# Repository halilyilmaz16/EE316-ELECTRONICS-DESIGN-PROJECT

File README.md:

# Capacitive Water Level Controller

An analog closed-loop water level control system designed and implemented
for the EE 316 Electronic Design Project at İzmir Institute of Technology.

The system detects liquid-level variations using a custom cylindrical
capacitive sensor. The sensor output is processed through phase detection,
filtering, amplification, error generation, and PWM stages. The resulting
PWM signal controls a submersible DC water pump through an L298N motor driver.

## Key Features

- Custom cylindrical capacitive water-level sensor
- TLC555-based oscillator
- XOR-based phase detection
- RC filtering and LM358 signal amplification
- Adjustable reference water level
- PWM-based pump speed control
- Motor overcurrent protection
- LTspice simulation and real-world circuit testing

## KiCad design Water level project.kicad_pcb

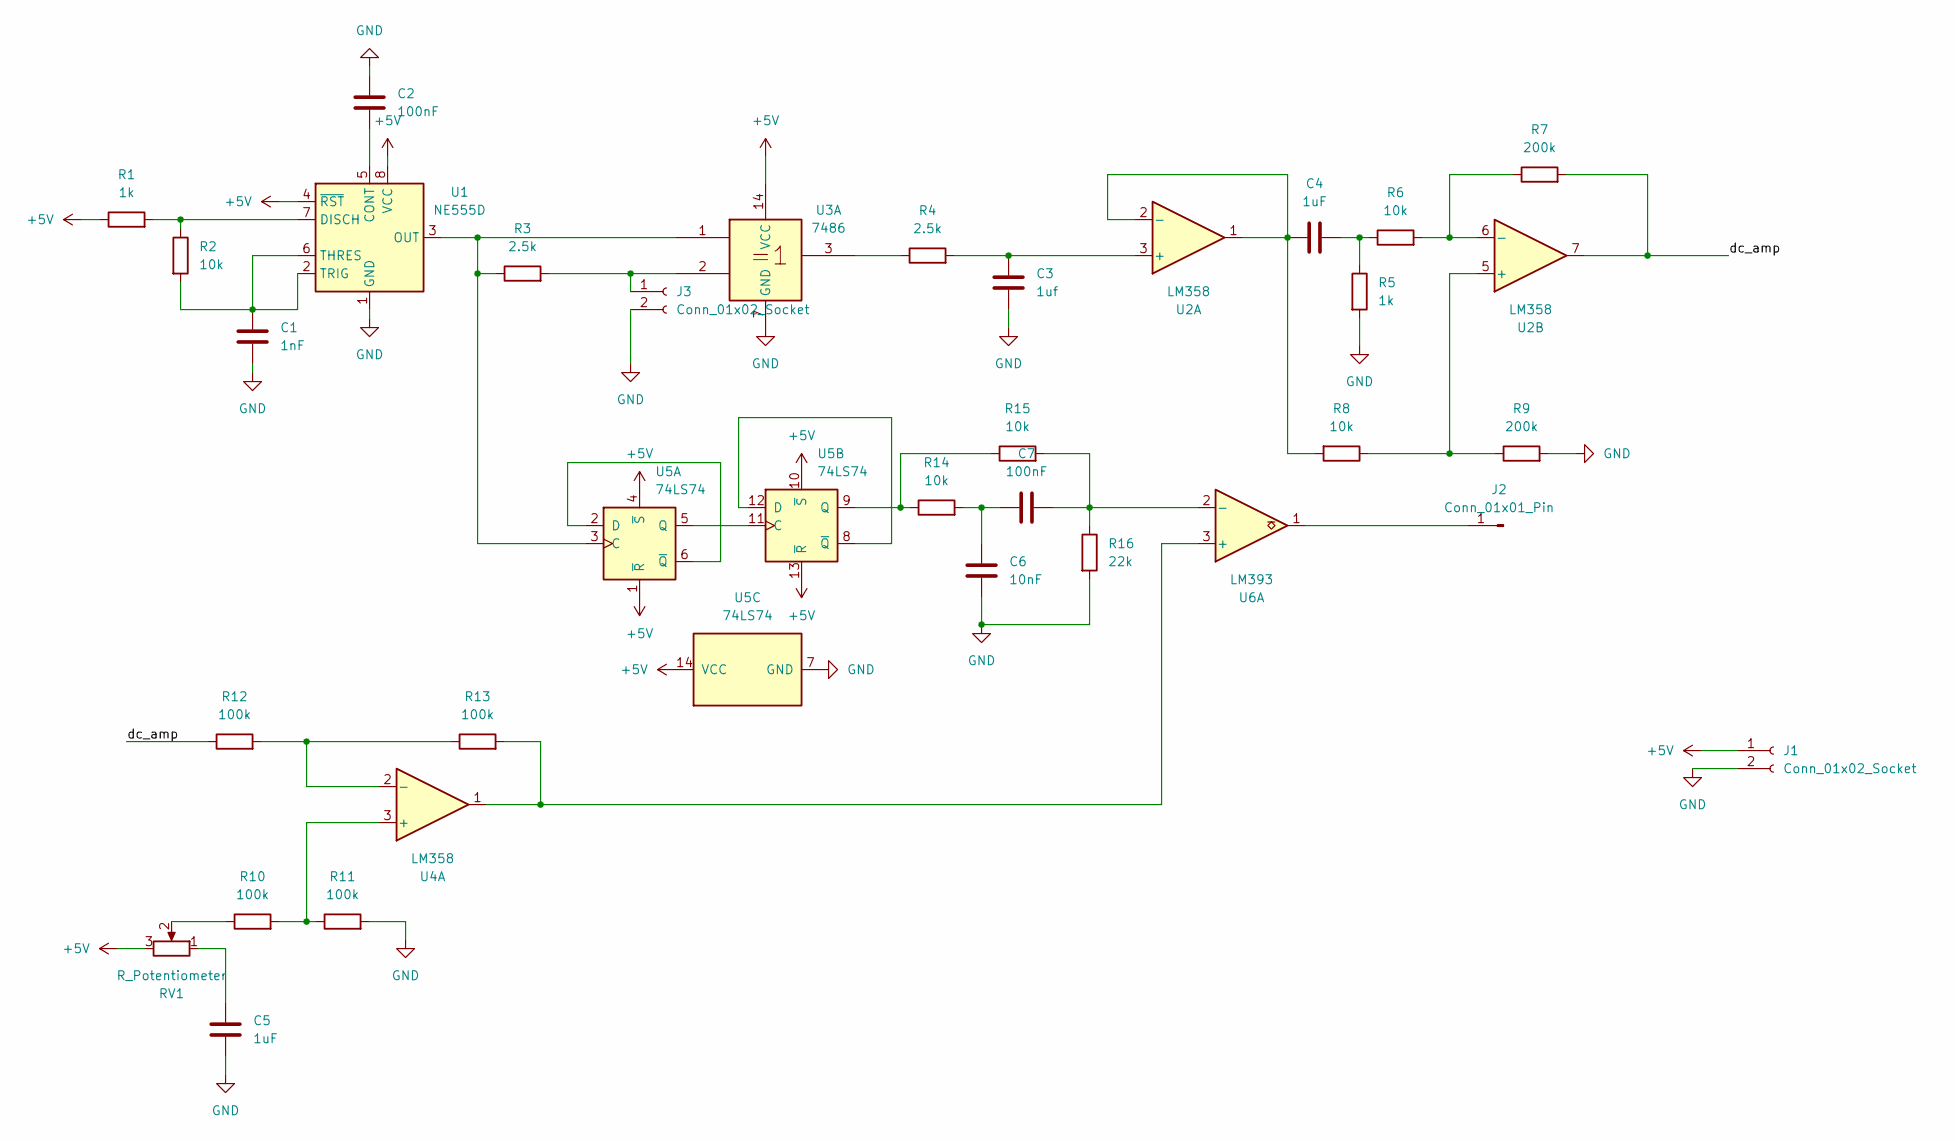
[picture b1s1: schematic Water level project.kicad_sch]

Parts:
C1: 1nF; C_Disc_D4.3mm_W1.9mm_P5.00mm
C2, C7: 100nF; C_Disc_D5.0mm_W2.5mm_P5.00mm
C3: 1uf; CP_Radial_D5.0mm_P2.50mm
C4, C5: 1uF; CP_Radial_D5.0mm_P2.50mm
C6: 10nF; C_Disc_D4.3mm_W1.9mm_P5.00mm
J1, J3: Conn_01x02_Socket; PinSocket_1x02_P2.54mm_Vertical
J2: Conn_01x01_Pin; PinSocket_1x01_P2.54mm_Vertical
R1, R5: 1k; R_Axial_DIN0207_L6.3mm_D2.5mm_P7.62mm_Horizontal
R2, R6, R8, R14, R15: 10k; R_Axial_DIN0207_L6.3mm_D2.5mm_P7.62mm_Horizontal
R3, R4: 2.5k; R_Axial_DIN0207_L6.3mm_D2.5mm_P7.62mm_Horizontal
R7, R9: 200k; R_Axial_DIN0207_L6.3mm_D2.5mm_P7.62mm_Horizontal
R10, R11, R12, R13: 100k; R_Axial_DIN0207_L6.3mm_D2.5mm_P7.62mm_Horizontal
R16: 22k; R_Axial_DIN0207_L6.3mm_D2.5mm_P7.62mm_Horizontal
RV1: R_Potentiometer; Potentiometer_Piher_PC-16_Single_Vertical
U1: NE555D; DIP-8_W7.62mm
U2, U4: LM358; DIP-8_W7.62mm
U3: 7486; DIP-14_W7.62mm
U5: 74LS74; DIP-14_W7.62mm
U6: LM393; DIP-8_W7.62mm

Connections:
+5V: J1.1, R1.1, RV1.3, U1.4 (~RST), U1.8 (VCC), U3.14 (VCC), U5.1 (~R), U5.4 (~S), U5.10 (~S), U5.13 (~R), U5.14 (VCC)
/dc_amp: R7.2, R12.1, U2.7
GND: C1.2, C2.1, C3.2, C5.2, C6.2, J1.2, J3.2, R5.2, R9.2, R11.2, R16.2, U1.1 (GND), U3.7 (GND), U5.7 (GND)
unnamed: C4.2, R5.1, R6.1
unnamed: C5.1, RV1.1
unnamed: C6.1, C7.1, R14.2
unnamed: J2.1 (Pin_1_1), U6.1
unnamed: J3.1, R3.2, U3.2
unnamed: R4.1, U3.3
unnamed: R10.1, RV1.2
unnamed: C2.2, U1.5 (CONT)
unnamed: R1.2, R2.1, U1.7 (DISCH)
unnamed: R3.1, U1.3 (OUT), U3.1, U5.3 (C)
unnamed: C1.1, R2.2, U1.2 (TRIG), U1.6 (THRES)
unnamed: C3.1, R4.2, U2.3 (+)
unnamed: C4.1, R8.2, U2.1, U2.2 (-)
unnamed: R8.1, R9.1, U2.5 (+)
unnamed: R6.2, R7.1, U2.6 (-)
unnamed: R10.2, R11.1, U4.3 (+)
unnamed: R12.2, R13.1, U4.2 (-)
unnamed: U5.2 (D), U5.6 (~Q)
unnamed: U5.5 (Q), U5.11 (C)
unnamed: U5.8 (~Q), U5.12 (D)
unnamed: R14.1, R15.1, U5.9 (Q)
unnamed: R13.2, U4.1, U6.3 (+)
unnamed: C7.2, R15.2, R16.1, U6.2 (-)

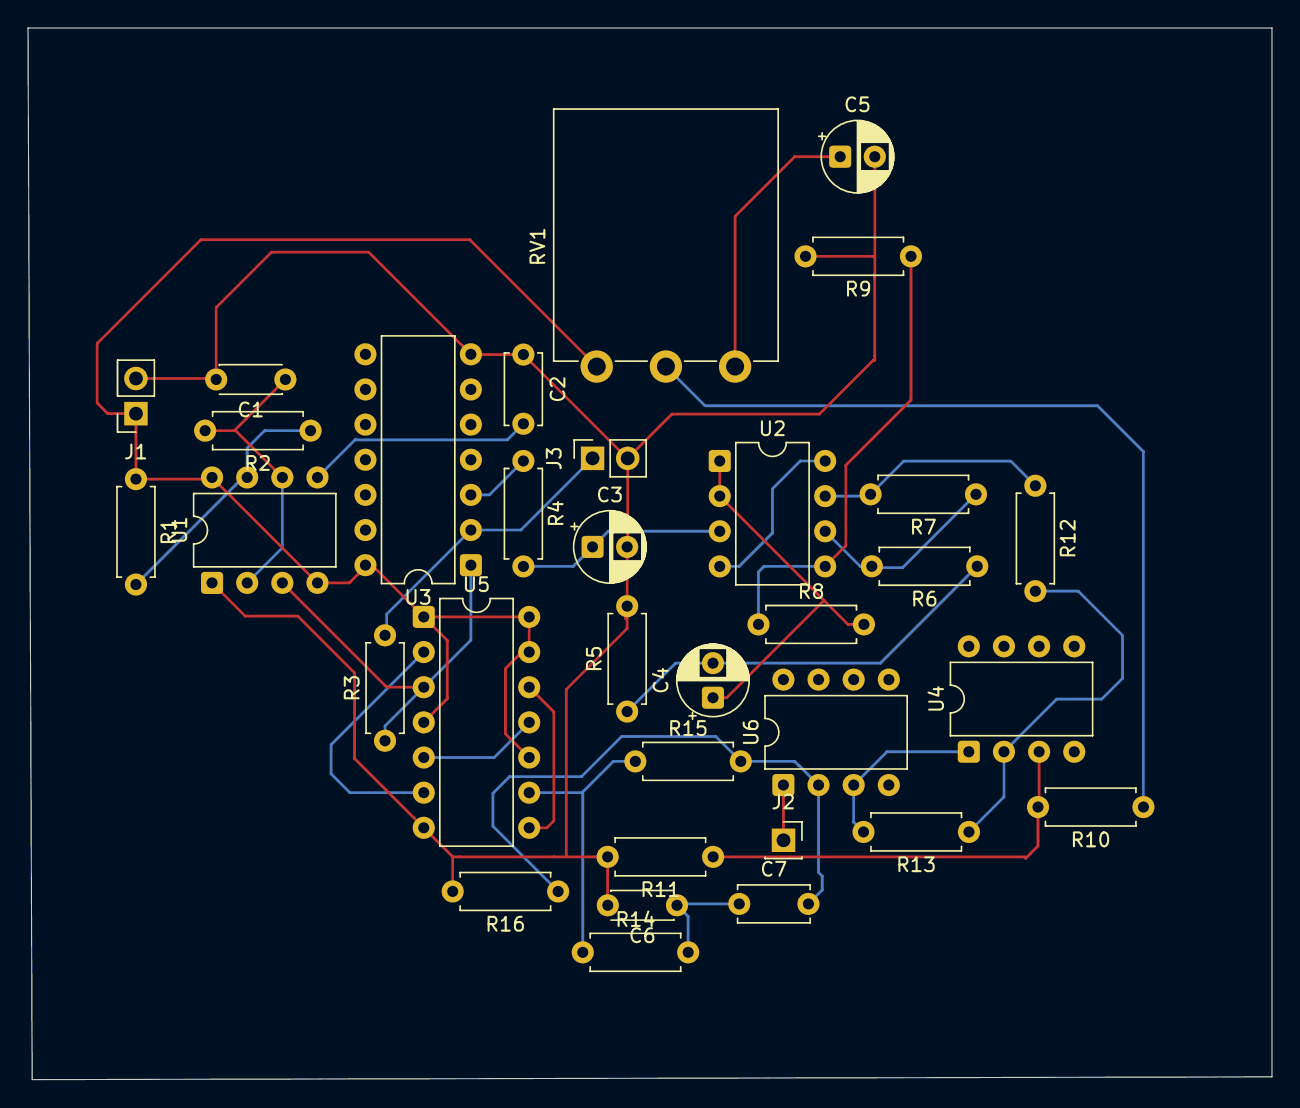
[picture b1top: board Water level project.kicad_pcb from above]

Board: 2 copper layers, 89.9 x 76.0 mm, 33 parts (0 on the bottom side), 26 nets.
